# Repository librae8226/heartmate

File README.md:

heartmate
=========

Originally based on pulse-sensor - http://pulsesensor.com/ .

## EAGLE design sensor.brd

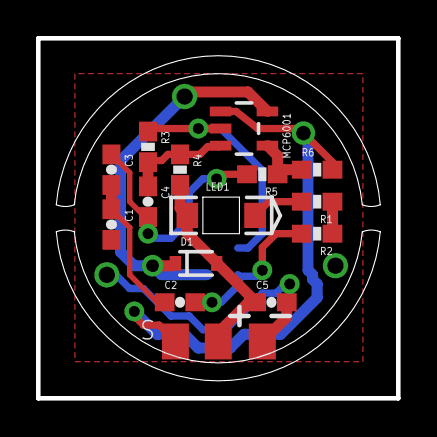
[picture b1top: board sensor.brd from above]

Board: 2 copper layers, 20.0 x 20.0 mm, 18 parts (1 on the bottom side), 10 nets.

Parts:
APDS1: MINIATURE-CHIPLED
C1, C2, C3: 4.7uF; 0603-CAP
C4, C5: 2.2uF; 0603-CAP
D1: BAT20JFILM; SOD-323
GND: M01SMD-4.5X1.5; PAD-1.5X4.5
LED1: LED-1206-REVERSE-MOUNT
MCP6001: OPA344; SOT23-5
OUT: M01SMD-4.5X1.5; PAD-1.5X4.5
R1: 470; 0603-RES
R2: 12K; 0603-RES
R3, R4: 100K; 0603-RES
R5: 10K; 0603-RES
R6: 3.3M; 0603-RES
VCC: M01SMD-4.5X1.5; PAD-1.5X4.5

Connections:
GND: APDS1.P$4, C1.2, C5.2, GND.P$1, MCP6001.2, R1.1, R2.1, R3.1
unnamed: LED1.C, R1.2
unnamed: MCP6001.4, R5.1, R6.1
unnamed: APDS1.P$6, C2.2, R2.2
unnamed: C1.1, C2.1, C3.2
unnamed: C3.1, C4.2, R5.2
unnamed: C4.1, MCP6001.3, R3.2, R4.1
OUT: MCP6001.1, OUT.P$1, R6.2
VCC: C5.1, D1.2, LED1.A, R4.2, VCC.P$1
VDD: APDS1.P$1, D1.1, MCP6001.5

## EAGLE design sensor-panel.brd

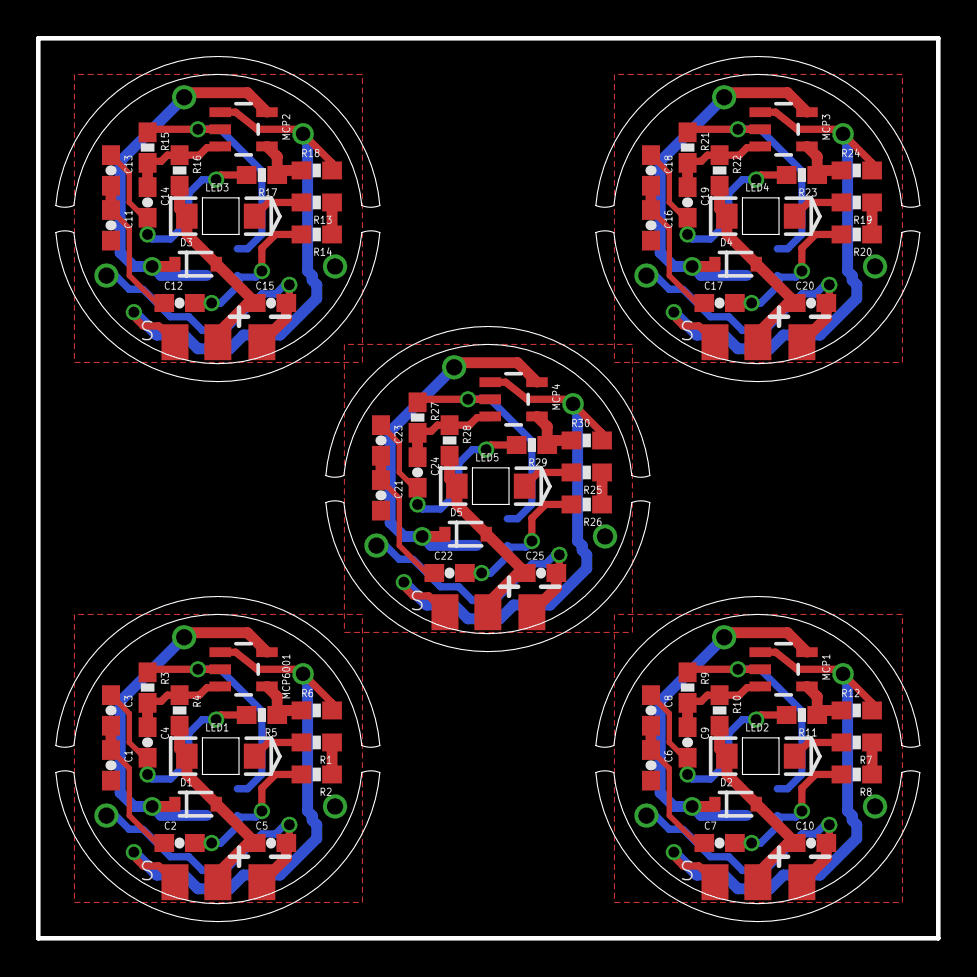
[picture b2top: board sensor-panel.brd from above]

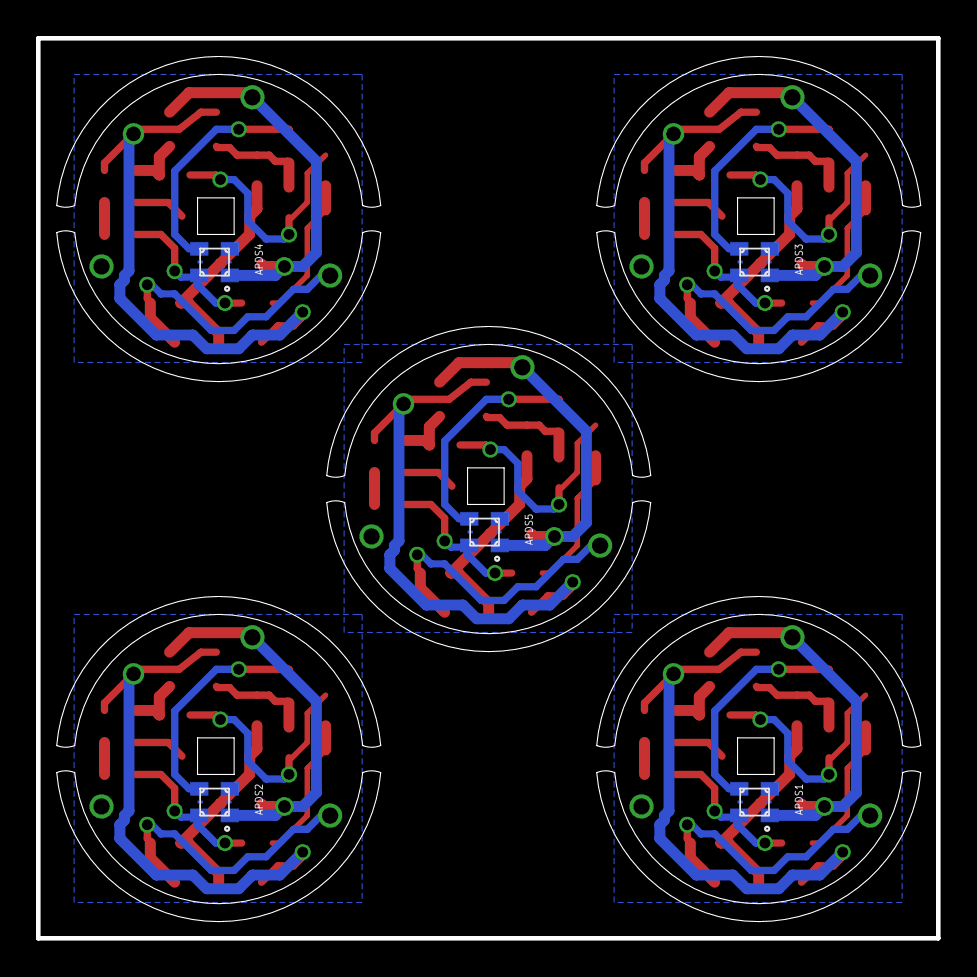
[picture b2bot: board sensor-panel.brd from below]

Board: 2 copper layers, 50.0 x 50.0 mm, 90 parts (5 on the bottom side), 50 nets.

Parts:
APDS1, APDS2, APDS3, APDS4, APDS5: MINIATURE-CHIPLED
C1, C2, C3, C6, C7, C8, C11, C12, C13, C16, C17, C18, C21, C22, C23: 4.7uF; 0603-CAP
C4, C5, C9, C10, C14, C15, C19, C20, C24, C25: 2.2uF; 0603-CAP
D1, D2, D3, D4, D5: BAT20JFILM; SOD-323
GND1, GND2, GND3, GND4, GND5: M01SMD-4.5X1.5; PAD-1.5X4.5
LED1, LED2, LED3, LED4, LED5: LED-1206-REVERSE-MOUNT
MCP1, MCP2, MCP3, MCP4, MCP6001: OPA344; SOT23-5
OUT1, OUT2, OUT3, OUT4, OUT5: M01SMD-4.5X1.5; PAD-1.5X4.5
R1, R7, R13, R19, R25: 470; 0603-RES
R2, R8, R14, R20, R26: 12K; 0603-RES
R3, R4, R9, R10, R15, R16, R21, R22, R27, R28: 100K; 0603-RES
R5, R11, R17, R23, R29: 10K; 0603-RES
R6, R12, R18, R24, R30: 3.3M; 0603-RES
VCC1, VCC2, VCC3, VCC4, VCC5: M01SMD-4.5X1.5; PAD-1.5X4.5

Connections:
GND: APDS1.P$4, C1.2, C5.2, GND1.P$1, MCP6001.2, R1.1, R2.1, R3.1
GND1: APDS2.P$4, C6.2, C10.2, GND2.P$1, MCP1.2, R7.1, R8.1, R9.1
GND2: APDS3.P$4, C11.2, C15.2, GND3.P$1, MCP2.2, R13.1, R14.1, R15.1
GND3: APDS4.P$4, C16.2, C20.2, GND4.P$1, MCP3.2, R19.1, R20.1, R21.1
GND4: APDS5.P$4, C21.2, C25.2, GND5.P$1, MCP4.2, R25.1, R26.1, R27.1
unnamed: LED2.C, R7.2
unnamed: APDS2.P$6, C7.2, R8.2
unnamed: LED1.C, R1.2
unnamed: C6.1, C7.1, C8.2
unnamed: C8.1, C9.2, R11.2
unnamed: MCP6001.4, R5.1, R6.1
unnamed: APDS1.P$6, C2.2, R2.2
unnamed: C1.1, C2.1, C3.2
unnamed: C3.1, C4.2, R5.2
unnamed: C4.1, MCP6001.3, R3.2, R4.1
unnamed: C9.1, MCP1.3, R9.2, R10.1
unnamed: MCP1.4, R11.1, R12.1
unnamed: LED3.C, R13.2
unnamed: APDS3.P$6, C12.2, R14.2
unnamed: C11.1, C12.1, C13.2
unnamed: C13.1, C14.2, R17.2
unnamed: C14.1, MCP2.3, R15.2, R16.1
unnamed: MCP2.4, R17.1, R18.1
unnamed: LED4.C, R19.2
unnamed: APDS4.P$6, C17.2, R20.2
unnamed: C16.1, C17.1, C18.2
unnamed: C18.1, C19.2, R23.2
unnamed: C19.1, MCP3.3, R21.2, R22.1
unnamed: MCP3.4, R23.1, R24.1
unnamed: LED5.C, R25.2
unnamed: APDS5.P$6, C22.2, R26.2
unnamed: C21.1, C22.1, C23.2
unnamed: C23.1, C24.2, R29.2
unnamed: C24.1, MCP4.3, R27.2, R28.1
unnamed: MCP4.4, R29.1, R30.1
OUT: MCP6001.1, OUT1.P$1, R6.2
OUT1: MCP1.1, OUT2.P$1, R12.2
OUT2: MCP2.1, OUT3.P$1, R18.2
OUT3: MCP3.1, OUT4.P$1, R24.2
OUT4: MCP4.1, OUT5.P$1, R30.2
VCC: C5.1, D1.2, LED1.A, R4.2, VCC1.P$1
VCC1: C10.1, D2.2, LED2.A, R10.2, VCC2.P$1
VCC2: C15.1, D3.2, LED3.A, R16.2, VCC3.P$1
VCC3: C20.1, D4.2, LED4.A, R22.2, VCC4.P$1
VCC4: C25.1, D5.2, LED5.A, R28.2, VCC5.P$1
VDD: APDS1.P$1, D1.1, MCP6001.5
VDD1: APDS2.P$1, D2.1, MCP1.5
VDD2: APDS3.P$1, D3.1, MCP2.5
VDD3: APDS4.P$1, D4.1, MCP3.5
VDD4: APDS5.P$1, D5.1, MCP4.5

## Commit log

2013-07-01 sensor: add sch and brd design file
    Also add a manufacture directory for specific stuffs.
2013-07-01 sensor: pcb route completed
2013-07-01 sensor: Apply 8mil DRC for pcb file.
    1. Reduce shottkey diode size from SMA to 0603
    2. Reduce board size.
2013-07-01 sensor: change file access mode
2013-07-01 sensor: fix apds-9008 package error
2013-07-02 sensor: update brd into a 20*20 rectangle
2013-07-02 sensor: panelization
2013-07-06 sensor: correct schematic and refine layout
    1. Replace fake schottkey with a *real* one.
    2. Refine polygon.
    3. Refine dimension.
    4. Refine panel.
    5. Add more blowholes (vias).
    6. Slightly refine some wires.
2013-07-06 Update README.
2013-07-07 manufacture: change file access permission
2013-07-07 doc: update draft and prototyping.
2013-07-07 doc: update draft.
2013-07-08 sensor: update lbr and correct design
    1. Add a reverse mount led.
    2. Update output pad.
2013-07-10 sensor: update pcb layout
    Mainly correct LED position and work mechanism.
2013-07-15 sensor: increase led hole size

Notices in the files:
parts and their libraries:
SparkFun-AnalogIC: Licensing: CC v3.0 Share-Alike You are welcome to use this library for commercial purposes.
